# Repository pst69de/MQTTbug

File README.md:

# MQTTbug
Board and code for MQTTbug project [(see also MQTTbug project page)](http://wiki69.pst69.homeip.net/index.php/Project_MQTTbug).

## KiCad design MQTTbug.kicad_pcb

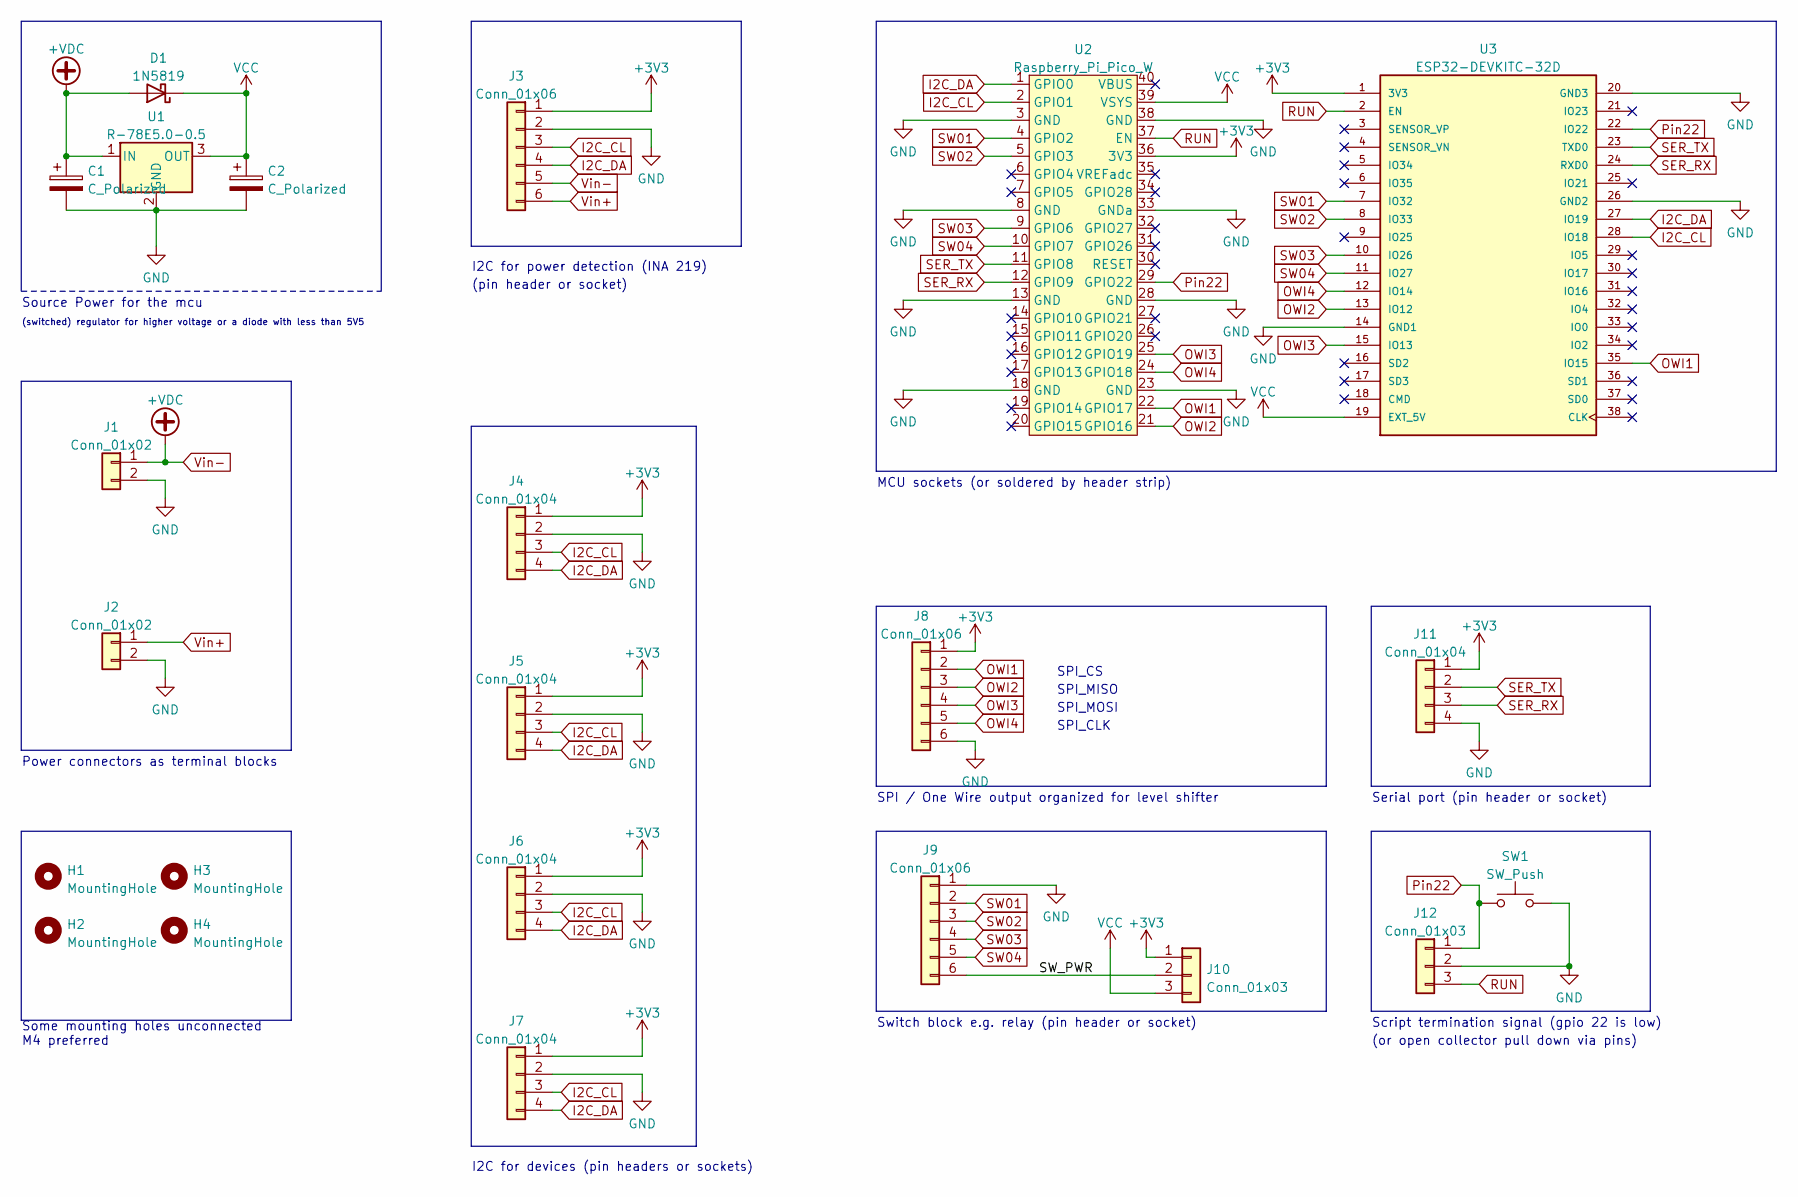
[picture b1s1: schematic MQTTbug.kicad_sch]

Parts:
C1, C2: C_Polarized; CP_Radial_D10.0mm_P2.50mm_P5.00mm
D1: 1N5819; D_DO-41_SOD81_P10.16mm_Horizontal
H1, H2, H3, H4: MountingHole; MountingHole_4.3mm_M4
J1, J2: Conn_01x02; TerminalBlock_Phoenix_MKDS-1,5-2-5.08_1x02_P5.08mm_Horizont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
J3: Conn_01x06; PinSocket_1x06_P2.54mm_Vertical
J4, J5, J6, J7, J11: Conn_01x04; PinSocket_1x04_P2.54mm_Vertical
J8, J9: Conn_01x06; PinHeader_1x06_P2.54mm_Vertical
J10, J12: Conn_01x03; PinHeader_1x03_P2.54mm_Vertical
SW1: SW_Push; SW_PUSH_6mm_H5mm
U1: R-78E5.0-0.5; Converter_DCDC_RECOM_R-78E-0.5_THT
U2: Raspberry_Pi_Pico_W; Raspberry_Pi_Pico_W_Socket
U3: ESP32-DEVKITC-32D; MODULE_ESP32-DEVKITC-32D; PARTREV 4

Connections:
+3V3: J3.1, J4.1, J5.1, J6.1, J7.1, J8.1, J10.1, J11.1, U2.36 (3V3), U3.1 (3V3)
/SW_PWR: J9.6, J10.2
GND: C1.2, C2.2, J1.2, J2.2, J3.2, J4.2, J5.2, J6.2, J7.2, J8.6, J9.1, J11.4, J12.2, SW1.2, U1.2 (GND), U2.3 (GND), U2.8 (GND), U2.13 (GND), U2.18 (GND), U2.23 (GND), U2.28 (GND), U2.33 (GNDa), U2.38 (GND), U3.14 (GND1), U3.20 (GND3), U3.26 (GND2)
I2C_CL: J3.3, J4.3, J5.3, J6.3, J7.3, U2.2 (GPIO1), U3.28 (IO18)
I2C_DA: J3.4, J4.4, J5.4, J6.4, J7.4, U2.1 (GPIO0), U3.27 (IO19)
OWI1: J8.2, U2.22 (GPIO17), U3.35 (IO15)
OWI2: J8.3, U2.21 (GPIO16), U3.13 (IO12)
OWI3: J8.4, U2.25 (GPIO19), U3.15 (IO13)
OWI4: J8.5, U2.24 (GPIO18), U3.12 (IO14)
Pin22: J12.1, SW1.1, U2.29 (GPIO22), U3.22 (IO22)
RUN: J12.3, U2.37 (EN), U3.2 (EN)
SER_RX: J11.3, U2.12 (GPIO9), U3.24 (RXD0)
SER_TX: J11.2, U2.11 (GPIO8), U3.23 (TXD0)
SW01: J9.2, U2.4 (GPIO2), U3.7 (IO32)
SW02: J9.3, U2.5 (GPIO3), U3.8 (IO33)
SW03: J9.4, U2.9 (GPIO6), U3.10 (IO26)
SW04: J9.5, U2.10 (GPIO7), U3.11 (IO27)
VCC: C2.1, D1.1 (K), J10.3, U1.3 (OUT), U2.39 (VSYS), U3.19 (EXT_5V)
Vin+: J2.1, J3.6
Vin-: C1.1, D1.2 (A), J1.1, J3.5, U1.1 (IN)

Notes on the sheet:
MCU sockets (or soldered by header strip)
SPI_CS
SPI_MOSI
(or open collector pull down via pins)
I2C for devices (pin headers or sockets)
Script termination signal (gpio 22 is low)
Serial port (pin header or socket)
Power connectors as terminal blocks
Some mounting holes unconnected M4 preferred
I2C for power detection (INA 219)
Source Power for the mcu
Switch block e.g. relay (pin header or socket)
(pin header or socket)
SPI_MISO
(switched) regulator for higher voltage or a diode with less than 5V5
SPI_CLK
SPI / One Wire output organized for level shifter

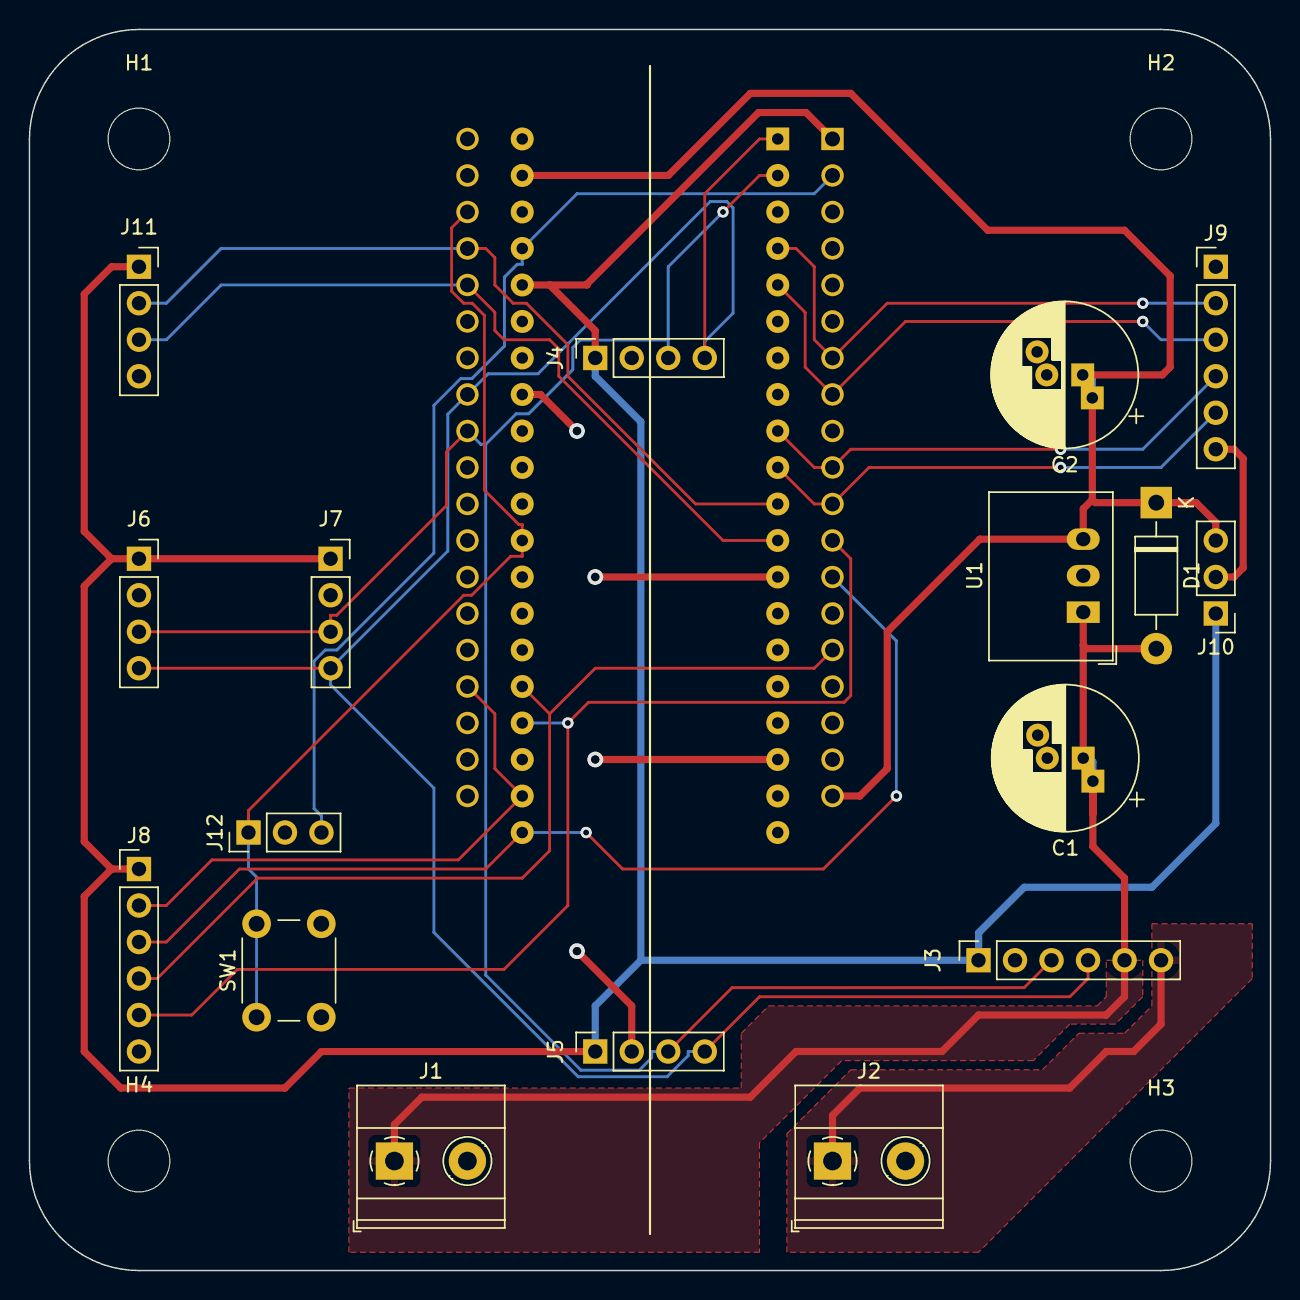
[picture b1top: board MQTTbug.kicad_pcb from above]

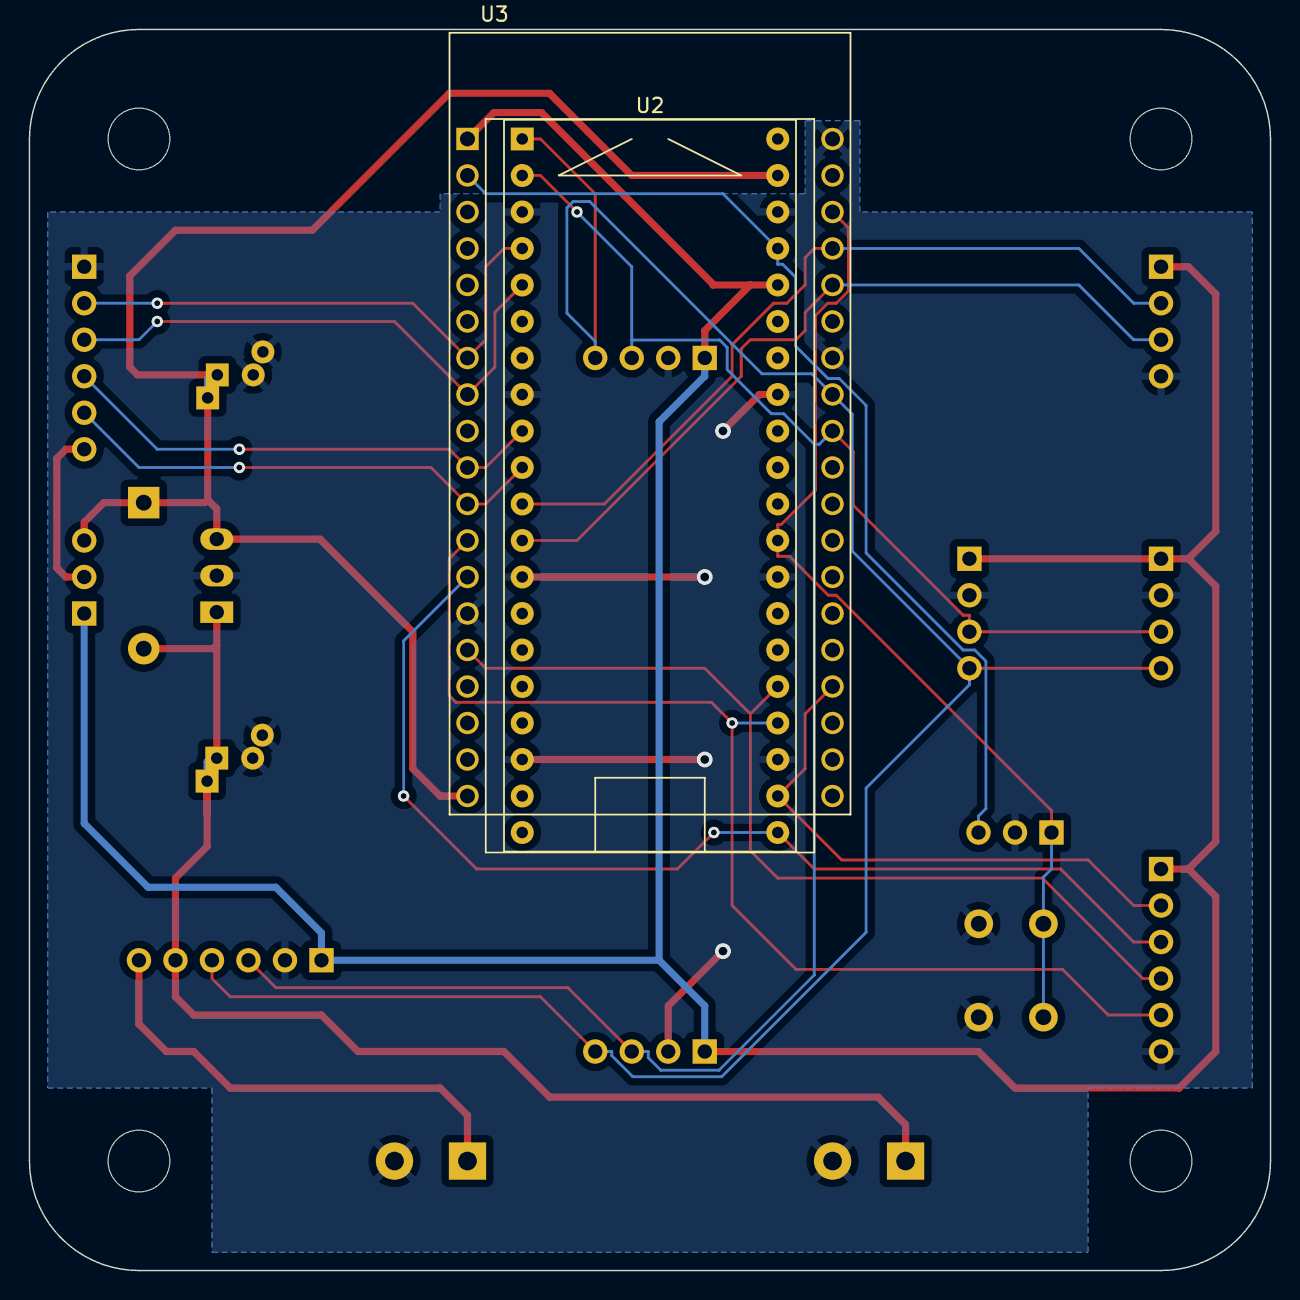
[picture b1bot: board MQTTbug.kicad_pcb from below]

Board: 2 copper layers, 86.4 x 86.4 mm, 23 parts (2 on the bottom side), 20 nets.

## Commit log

2023-02-02 1st commit: KiCad project file
2023-02-02 2nd commit: KiCad files
2023-02-02 3rd commit: mpy code files
2023-02-02 README.md: link project page
2023-02-08 2023-02-08: worked on PCB layout
2023-02-18 Finishing board layout manual and with autorouter
2023-02-19 last mods and first Gerber to PCB manufacturer
2023-03-19 start including library files (for later binding)
2023-03-19 show measure without net/mqtt
2023-03-19 corrected netfree/neted configuration
